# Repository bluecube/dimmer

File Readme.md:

LED Dimmer
==========

This is a PWM dimmer for 5-24V LED lighting, up to 5A.
Intended to  be mounted as an in-line cord switch.

Only eats couple μA of power when turned off.

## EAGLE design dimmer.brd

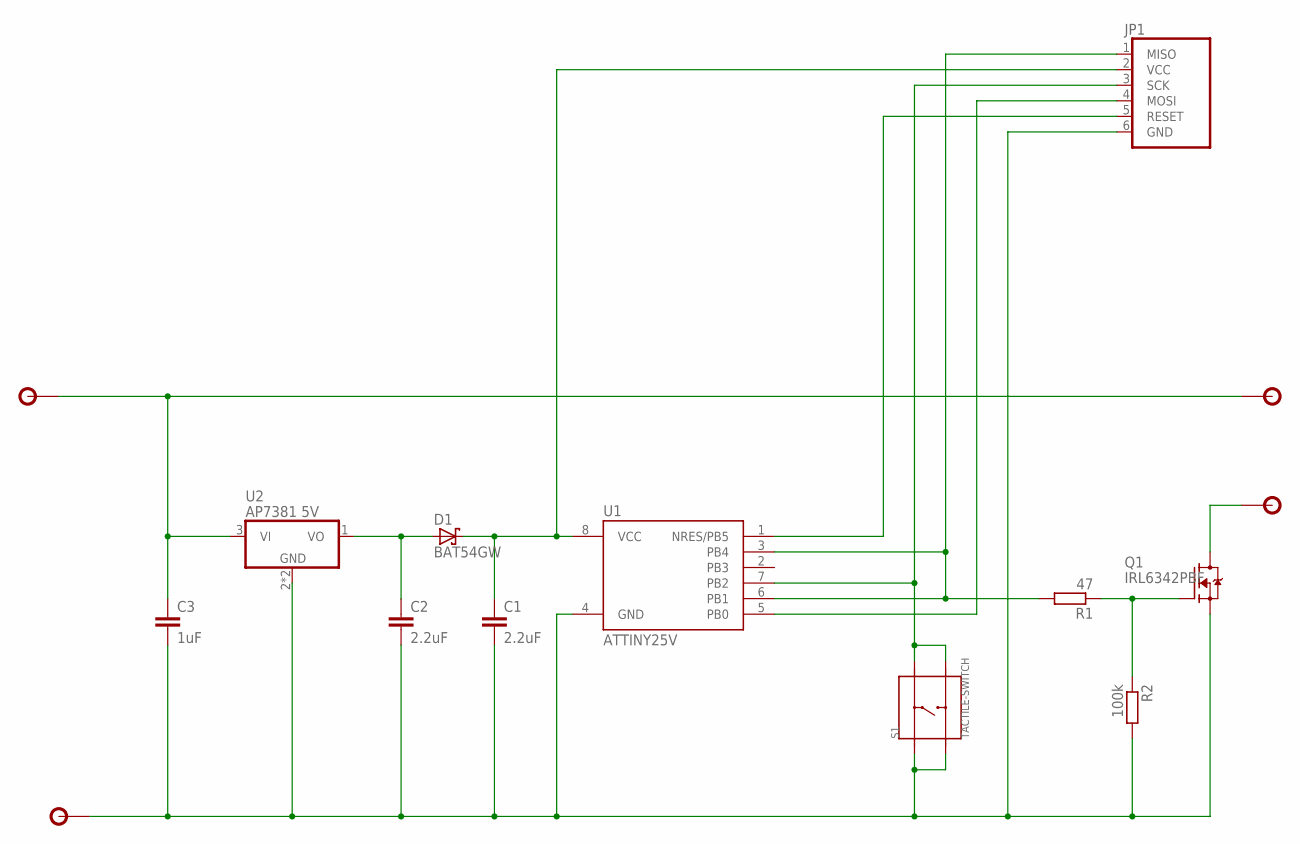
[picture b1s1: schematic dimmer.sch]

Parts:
C1, C2: 2.2uF; C0805
C3: 1uF; C0805
D1: BAT54GW; SOD123FL
JP1: AVR-ISP-6PIN; 2X03
Q1: IRL6342PBF; SO-8
R1: 47; R0805
R2: 100k; R0805
S1: TACTILE-SWITCH; SW4-SMD-4.5MM
U1: ATTINY25V; SOIC8_EIAJ_208MIL
U2: AP7381 5V; SOT89
X1, X2, X3, X4: PAD; PAD-L

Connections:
BTN: JP1.3 (SCK), S1.P$2 (A1), S1.P$4 (B1), U1.7 (PB2)
GND: C1.2, C2.2, C3.2, JP1.6 (GND), Q1.1 (S), Q1.2 (S), Q1.3 (S), R2.2, S1.P$1 (A0), S1.P$3 (B0), U1.4 (GND), U2.2 (GND), U2.2@1 (GND), X2.P$1
unnamed: C2.1, D1.A, U2.1 (VO)
unnamed: JP1.4 (MOSI), U1.5 (PB0)
unnamed: JP1.5 (RESET), U1.1 (NRES/PB5)
unnamed: Q1.4 (G), R1.1, R2.1
OUT: Q1.5 (D), Q1.6 (D), Q1.7 (D), Q1.8 (D), X4.P$1
PWM: JP1.1 (MISO), R1.2, U1.3 (PB4), U1.6 (PB1)
V+: C3.1, U2.3 (VI), X1.P$1, X3.P$1
VCC: C1.1, D1.C, JP1.2 (VCC), U1.8 (VCC)

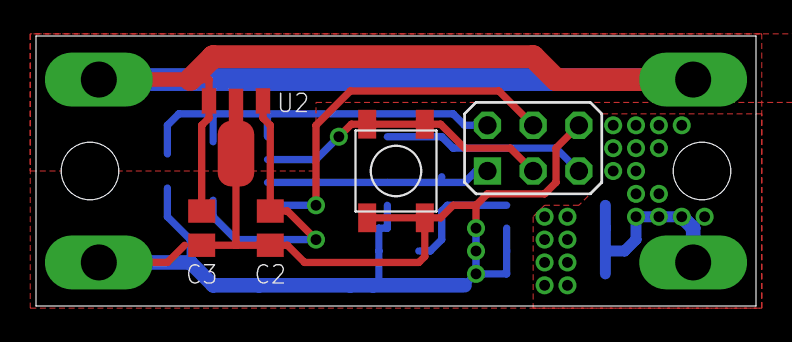
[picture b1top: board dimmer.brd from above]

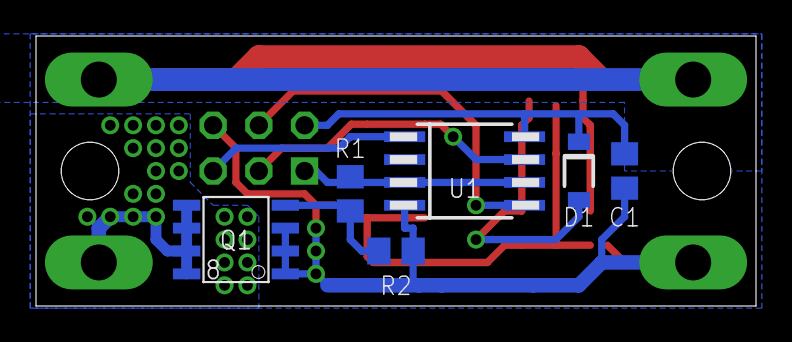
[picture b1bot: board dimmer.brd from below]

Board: 2 copper layers, 40.0 x 15.0 mm, 15 parts (6 on the bottom side), 10 nets.

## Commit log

2019-10-18 Added Readme file
2019-10-18 Almost finished hardware design.
2019-10-18 Finished case
2019-10-20 Added gitignore
2019-10-20 Board sent for manufacturing.
2019-10-25 Started working on the source code, very much WIP.
2019-11-01 More WIP code
